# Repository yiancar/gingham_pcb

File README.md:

Gingham
================

The ANSI/ISO keyboard kit made using ONLY through hole components and inspired by the [Plaid](https://github.com/hsgw/plaid).

Atmega328p with VUSB on [QMK firmware](https://github.com/qmk/qmk_firmware).

To alter the pcb use KiCAD V5.0 or newer as it already contains most of the libraries. The additional libraries are provided.

License
===========

This project is licensed under the [Creative Commons Attribution-NonCommercial 4.0 International License](https://creativecommons.org/licenses/by-nc/4.0/).

If you have remixed, adapted or build upon this work and wish to remove the non-commercial clause for your own project please contact me at https://www.yiancar-designs.com. Your request is more than likely to be granted. The non-commercial part of the license is intended to avoid direct copies of the work to be sold for commercial gain by third parties.

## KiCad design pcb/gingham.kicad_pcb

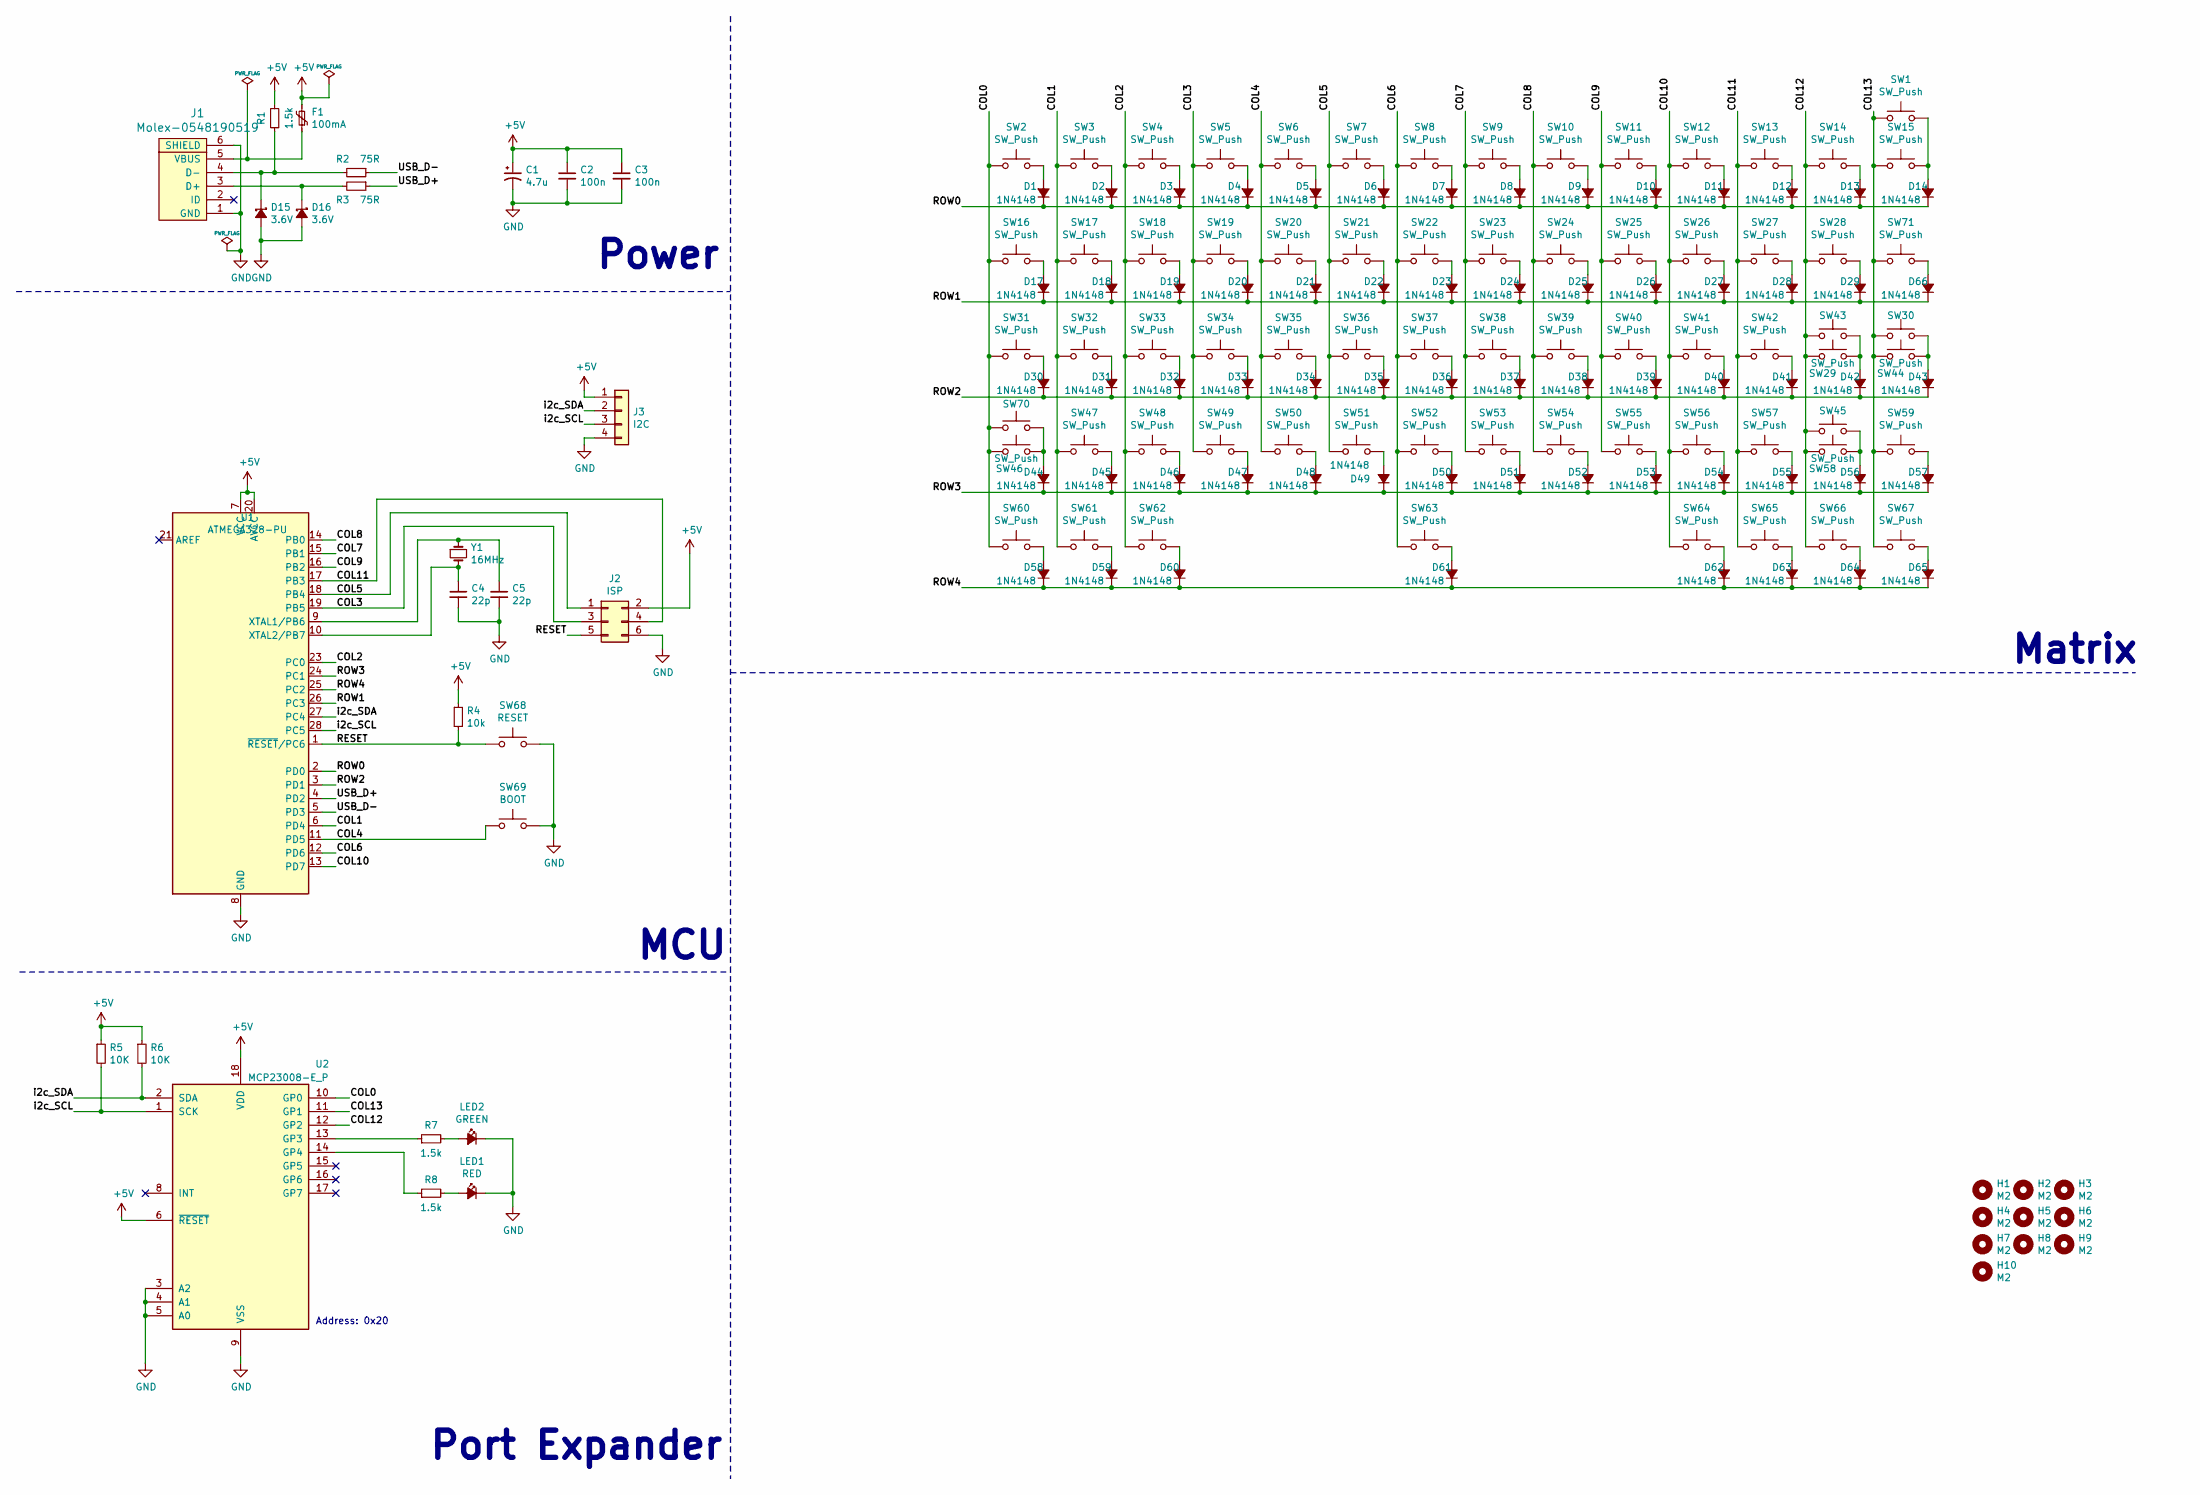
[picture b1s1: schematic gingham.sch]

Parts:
C1: 4.7u; CP_Radial_D4.0mm_P1.50mm
C2, C3: 100n; C_Disc_D4.3mm_W1.9mm_P5.00mm
C4, C5: 22p; C_Disc_D3.0mm_W1.6mm_P2.50mm
D1, D2, D3, D4, D5, D6, D7, D8, D9, D10, D11, D12, D13, D14, D17, D18, D19, D20, D21, D22, D23, D24, D25, D26, D27, D28, D29, D30, D31, D32, D33, D34, D35, D36, D37, D38, D39, D40, D41, D42, D43, D44, D45, D46, D47, D48, D49, D50, D51, D52, D53, D54, D55, D56, D57, D58, D59, D60, D61, D62, D63, D64, D65, D66: 1N4148; D_DO-35_SOD27_P7.62mm_Horizontal
D15, D16: 3.6V; D_DO-35_SOD27_P7.62mm_Horizontal
F1: 100mA; C_Disc_D5.0mm_W2.5mm_P5.00mm
H1, H2, H3, H4, H5, H6, H7, H8, H9, H10: M2; MountingHole_2.2mm_M2_DIN965_Pad
J1: Molex-0548190519
J2: ISP; PinHeader_2x03_P2.54mm_Vertical
J3: I2C; PinHeader_1x04_P2.54mm_Vertical
LED1: RED; LED_D3.0mm_Clear
LED2: GREEN; LED_D3.0mm_Clear
R1, R7, R8: 1.5k; R_Axial_DIN0204_L3.6mm_D1.6mm_P5.08mm_Horizontal
R2, R3: 75R; R_Axial_DIN0204_L3.6mm_D1.6mm_P5.08mm_Horizontal
R4: 10k; R_Axial_DIN0204_L3.6mm_D1.6mm_P5.08mm_Horizontal
R5, R6: 10K; R_Axial_DIN0204_L3.6mm_D1.6mm_P5.08mm_Horizontal
SW1: SW_Push; MX-2U-NoLED
SW2, SW3, SW4, SW5, SW6, SW7, SW8, SW9, SW10, SW11, SW12, SW13, SW14, SW15, SW17, SW18, SW19, SW20, SW21, SW22, SW23, SW24, SW25, SW26, SW27, SW28, SW29, SW32, SW33, SW34, SW35, SW36, SW37, SW38, SW39, SW40, SW41, SW42, SW47, SW48, SW49, SW50, SW51, SW52, SW53, SW54, SW55, SW56, SW57, SW59, SW71: SW_Push; MX-1U-NoLED
SW16, SW43: SW_Push; MX-1.5U-NoLED
SW30: SW_Push; MX-ISO-ReversedStabilizers
SW31, SW45: SW_Push; MX-1.75U-NoLED
SW44, SW46: SW_Push; MX-2.25U-NoLED
SW58: SW_Push; MX-2.75U-NoLED
SW60, SW61, SW62, SW64, SW65, SW66, SW67, SW70: SW_Push; MX-1.25U-NoLED
SW63: SW_Push; MX-6.25U-ReversedStabilizers-NoLED
SW68: RESET; SW_PUSH_6mm
SW69: BOOT; SW_PUSH_6mm
U1: ATMEGA328-PU; DIP-28_W7.62mm
U2: MCP23008-E_P; DIP-18_W7.62mm
Y1: 16MHz; Crystal_HC49-4H_Vertical

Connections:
+5V: C1.1, C2.1, C3.1, F1.2, J2.2, J3.1, R1.2, R4.1, R5.1, R6.1, U1.7 (VCC), U1.20 (AVCC), U2.6 (~RESET~), U2.18 (VDD)
/COL0: SW2.2, SW16.2, SW31.2, SW46.2, SW60.2, SW70.2, U2.10 (GP0)
/COL1: SW3.2, SW17.2, SW32.2, SW47.2, SW61.2, U1.6 (PD4)
/COL2: SW4.2, SW18.2, SW33.2, SW48.2, SW62.2, U1.23 (PC0)
/COL3: J2.3, SW5.2, SW19.2, SW34.2, SW49.2, U1.19 (PB5)
/COL4: SW6.2, SW20.2, SW35.2, SW50.2, SW69.1, U1.11 (PD5)
/COL5: J2.1, SW7.2, SW21.2, SW36.2, SW51.2, U1.18 (PB4)
/COL6: SW8.2, SW22.2, SW37.2, SW52.2, SW63.2, U1.12 (PD6)
/COL7: SW9.2, SW23.2, SW38.2, SW53.2, U1.15 (PB1)
/COL8: SW10.2, SW24.2, SW39.2, SW54.2, U1.14 (PB0)
/COL9: SW11.2, SW25.2, SW40.2, SW55.2, U1.16 (PB2)
/COL10: SW12.2, SW26.2, SW41.2, SW56.2, SW64.2, U1.13 (PD7)
/COL11: J2.4, SW13.2, SW27.2, SW42.2, SW57.2, SW65.2, U1.17 (PB3)
/COL12: SW14.2, SW28.2, SW29.2, SW43.2, SW45.2, SW58.2, SW66.2, U2.12 (GP2)
/COL13: SW1.2, SW15.2, SW30.2, SW44.2, SW59.2, SW67.2, SW71.2, U2.11 (GP1)
/RESET: J2.5, R4.2, SW68.1, U1.1 (~RESET~/PC6)
/ROW0: D1.1 (K), D2.1 (K), D3.1 (K), D4.1 (K), D5.1 (K), D6.1 (K), D7.1 (K), D8.1 (K), D9.1 (K), D10.1 (K), D11.1 (K), D12.1 (K), D13.1 (K), D14.1 (K), U1.2 (PD0)
/ROW1: D17.1 (K), D18.1 (K), D19.1 (K), D20.1 (K), D21.1 (K), D22.1 (K), D23.1 (K), D24.1 (K), D25.1 (K), D26.1 (K), D27.1 (K), D28.1 (K), D29.1 (K), D66.1 (K), U1.26 (PC3)
/ROW2: D30.1 (K), D31.1 (K), D32.1 (K), D33.1 (K), D34.1 (K), D35.1 (K), D36.1 (K), D37.1 (K), D38.1 (K), D39.1 (K), D40.1 (K), D41.1 (K), D42.1 (K), D43.1 (K), U1.3 (PD1)
/ROW3: D44.1 (K), D45.1 (K), D46.1 (K), D47.1 (K), D48.1 (K), D49.1 (K), D50.1 (K), D51.1 (K), D52.1 (K), D53.1 (K), D54.1 (K), D55.1 (K), D56.1 (K), D57.1 (K), U1.24 (PC1)
/ROW4: D58.1 (K), D59.1 (K), D60.1 (K), D61.1 (K), D62.1 (K), D63.1 (K), D64.1 (K), D65.1 (K), U1.25 (PC2)
/USB_D+: R3.1, U1.4 (PD2)
/USB_D-: R2.1, U1.5 (PD3)
/i2c_SCL: J3.3, R5.2, U1.28 (PC5), U2.1 (SCK)
/i2c_SDA: J3.2, R6.2, U1.27 (PC4), U2.2 (SDA)
GND: C1.2, C2.2, C3.2, C4.2, C5.2, D15.2 (A), D16.2 (A), J1.1 (GND), J1.6 (SHIELD), J2.6, J3.4, LED1.1 (K), LED2.1 (K), SW68.2, SW69.2, U1.8 (GND), U1.22 (GND), U2.3 (A2), U2.4 (A1), U2.5 (A0), U2.9 (VSS)
unnamed: C4.1, U1.10 (XTAL2/PB7), Y1.2
unnamed: C5.1, U1.9 (XTAL1/PB6), Y1.1
unnamed: D1.2 (A), SW2.1
unnamed: D2.2 (A), SW3.1
unnamed: D3.2 (A), SW4.1
unnamed: D4.2 (A), SW5.1
unnamed: D5.2 (A), SW6.1
unnamed: D6.2 (A), SW7.1
unnamed: D7.2 (A), SW8.1
unnamed: D8.2 (A), SW9.1
unnamed: D9.2 (A), SW10.1
unnamed: D10.2 (A), SW11.1
unnamed: D11.2 (A), SW12.1
unnamed: D12.2 (A), SW13.1
unnamed: D13.2 (A), SW14.1
unnamed: D14.2 (A), SW1.1, SW15.1
unnamed: D15.1 (K), J1.4 (D-), R1.1, R2.2
unnamed: D16.1 (K), J1.3 (D+), R3.2
unnamed: D17.2 (A), SW16.1
unnamed: D18.2 (A), SW17.1
unnamed: D19.2 (A), SW18.1
unnamed: D20.2 (A), SW19.1
unnamed: D21.2 (A), SW20.1
unnamed: D22.2 (A), SW21.1
unnamed: D23.2 (A), SW22.1
unnamed: D24.2 (A), SW23.1
unnamed: D25.2 (A), SW24.1
unnamed: D26.2 (A), SW25.1
unnamed: D27.2 (A), SW26.1
unnamed: D28.2 (A), SW27.1
unnamed: D29.2 (A), SW28.1
unnamed: D30.2 (A), SW31.1
unnamed: D31.2 (A), SW32.1
unnamed: D32.2 (A), SW33.1
unnamed: D33.2 (A), SW34.1
unnamed: D34.2 (A), SW35.1
unnamed: D35.2 (A), SW36.1
unnamed: D36.2 (A), SW37.1
unnamed: D37.2 (A), SW38.1
unnamed: D38.2 (A), SW39.1
unnamed: D39.2 (A), SW40.1
unnamed: D40.2 (A), SW41.1
unnamed: D41.2 (A), SW42.1
unnamed: D42.2 (A), SW29.1, SW43.1
unnamed: D43.2 (A), SW30.1, SW44.1
unnamed: D44.2 (A), SW46.1, SW70.1
unnamed: D45.2 (A), SW47.1
unnamed: D46.2 (A), SW48.1
unnamed: D47.2 (A), SW49.1
unnamed: D48.2 (A), SW50.1
unnamed: D49.2 (A), SW51.1
unnamed: D50.2 (A), SW52.1
unnamed: D51.2 (A), SW53.1
unnamed: D52.2 (A), SW54.1
unnamed: D53.2 (A), SW55.1
unnamed: D54.2 (A), SW56.1
unnamed: D55.2 (A), SW57.1
unnamed: D56.2 (A), SW45.1, SW58.1
unnamed: D57.2 (A), SW59.1
unnamed: D58.2 (A), SW60.1
unnamed: D59.2 (A), SW61.1
unnamed: D60.2 (A), SW62.1
unnamed: D61.2 (A), SW63.1
unnamed: D62.2 (A), SW64.1
unnamed: D63.2 (A), SW65.1
unnamed: D64.2 (A), SW66.1
unnamed: D65.2 (A), SW67.1
unnamed: D66.2 (A), SW71.1
unnamed: F1.1, J1.5 (VBUS)
unnamed: LED1.2 (A), R8.2
unnamed: LED2.2 (A), R7.2
unnamed: R7.1, U2.13 (GP3)
unnamed: R8.1, U2.14 (GP4)

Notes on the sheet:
Power
Matrix
MCU
Port Expander
Address: 0x20

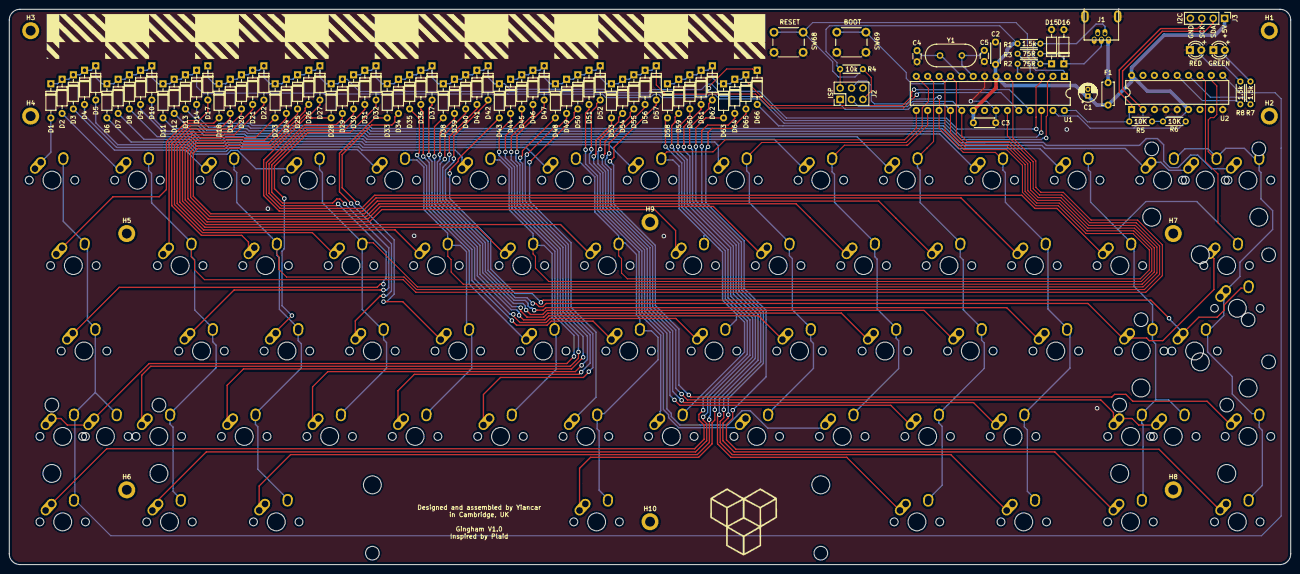
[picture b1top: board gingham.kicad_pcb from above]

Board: 2 copper layers, 285.8 x 123.8 mm, 170 parts (0 on the bottom side), 99 nets.

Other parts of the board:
svg2mod: G***; gingham

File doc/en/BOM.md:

# BOM 
## Interactive web page
- To interactively see the BOM press [here](../../pcb/bom/ibom.html).  

## Included in Gingham kit
|                                   | Ref         | Qty | Value               | Description                                 |
|-----------------------------------|-------------|-----|---------------------|---------------------------------------------|
| ![22pF](../img/parts/P1020154.JPG) | C4, C5      | 2   | 22p                 | Multi layer ceramic capacitor (2.5mm pitch) |
| ![4.7uF](../img/parts/P1020157.JPG)              | C1          | 1   | 4.7u                | Electrolytic capacitor (1.5mm pitch)        |
| ![100nF](../img/parts/P1020155.JPG)              | C2, C3      | 2   | 100n                | Multi layer ceramic capacitor (5mm pitch)   |
| ![1N4148](../img/parts/P1020138.JPG)              | D1-66 (not D15, D16)       | 64  | 1N4148              | General-purpose diode (DO-35)               |
| ![3.6V](../img/parts/P1020151.JPG)              | D15, D16    | 2   | 3.6V                | 3.6V zener diode (DO-35)                 |
| ![fuse](../img/parts/P1020156.JPG)              | F1          | 1   | 100mA               | Resettable fuse (5mm pitch)                 |
| ![USB](../img/parts/P1020147.JPG)              | J1          | 1   | USB MINI-B          | USB miniB connector                         |
| ![2x3](../img/parts/P1020158.JPG)              | J2          | 1   | 02x03               | AVR ISP pin header                          |
| ![LED](../img/parts/P1020159.JPG)              | LED1,2      | 2   | RED, GREEN              | 3mm LED                                     |
| ![1.5k](../img/parts/P1020161.JPG)              | R1, R7, R8  | 3   | 1.5k                | 1/6W resistor                               |
| ![75R](../img/parts/P1020160.JPG)              | R2, R3      | 2   | 75R                 | 1/6W resistor                               |
| ![10k](../img/parts/P1020162.JPG)              | R4, R5, R6          | 3   | 10k                 | 1/6W resistor                               |
| ![](../img/parts/P1020153.JPG)              | SW68, SW69     | 2   | RESET, BOOT         | 6mm tactile switch                          |
| ![](../img/parts/P1020149.JPG)              | U1          | 1   | ATMEGA328P          |                                             |
| ![](../img/parts/P1020148.JPG)              | IC Socket   | 1   | 28pin               | 28pin IC Socket                             |
| ![](../img/parts/P1020149)              | U2          | 1   | MCP23008          |                                             |
| ![](../img/parts/P1020148)              | IC Socket   | 1   | 18pin               | 18pin IC Socket                             |
| ![](../img/parts/P1020150.JPG)              | Y1          | 1   | 16MHz               |                                             |
|                                    | Screw       | 14  | M2 8mm              |                                             |
|                                    | Nut         | 26  | M2                  |                                             |
|                                    | Spacer      | 4   | M2 10mm             |                                             |
|                                    | Rubber Feet | 4   |                     |                                             |
|                                   | PCB         | 1   | MAIN PCB            |                                             |
|                                   | PCB         | 1   | BOTTOM PCB          |                                             |

## Not included
- Cherry MX compatible switches * 64 (Depending on layout)   
**PCB mount (5pin) type**

- Mini-B USB cable

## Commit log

2019-05-29 Gingaham
2019-06-27 Final prep
2019-08-03 Relocate middle screwmounts
2020-06-18 Update LICENSE
2020-06-18 Updated License
